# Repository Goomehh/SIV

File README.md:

# SIV

Sistema de identificacion vehicular

# Info

Video presentacion del proyecto: https://youtu.be/XcQt5sAtSic (Principal)

El modelado de la caja y la placa de las conexiones usadas se encuentran en el apartado "Fotos" y "Videos"

# Poster Ingenia Futuro

Poster enfocado a la problematica junto a la propuesta de solucion presentada

# Idea principal del funcionamiento del sistema (flow-chart)

Dos diagramas independientes pero que hacen parte del mismo objetivo.
Como se puede ver en la primera parte del diagrama, el proyecto esta principalemtne orientado a las motos, esto debido a su inidice de hurto en la capital y la accesibilidad que se tiene a sus componentes internos.

Por otro lado esta el sistema de la aplicacion movil, este cuanto mas es parte escencial del proyecto, pues es la que permite el ingreso de nuevos usuarios al sistema y ubica la moto en tiempo real para transmitirlo graficamente

# Boceto superficial del funcionamiento del sistema

Se hace una idea de como puede quedar instalado el circuito en la moto.
De la misma forma se grafica como iria linealmente la secuencia de pasos necesaria para que el motor de la moto sea prendido.

# Diagrama de caja negra

Se plantea lo que viene siendo la alimentacion del circuito y de la misma forma la secuencia adecuada para el procesamiento de los datos, esto teniendo en cuenta el diagrama de flujo que nos explica como debe funcionar el circuito, es necesario tener en cuenta los componenetes principales de cada sector, es decir, los puntos vitales que requiere el circuito, como la alimentacion, el "cerebro", los actuadores, sensores, entre otros.

# Diagrama de caja negra con tecnologia definida

Una vez definida la dinamica y funcionamiento del circuito se empiezan a buscar componentes aptos para facilitar el ensamble, programacion y adaptacion, en nuestro caso usaremos componentes especificos como lo son el Esp32, un sensor de huellas fpm10a, un modulo sim para la tarjeta SD, entre otros (Lista completa en la seccion "Materiales").

# Esquematico del circuito 

En esta seccion se pretende diseñar de forma clara y organizada la conexion de los diferentes componentes que se van a implementar de forma que en caso de requerir fabricar una PCB, no haya mayor complicacion, el circuito fue hecho mediante la aplicacion Kicad.

# Esquematico de la placa PCB

En este esqumatico se puede apreciar la ubicacion de cada uno de los compenetes presentados anteriormente, a excepcion de los pulsadores que simulan al teclado, para este se ponen los puertos para soldar, por otro lado tambien se aprecian las conexiones que se realizan de forma que se ahorra bastante espacio, este tipo de conexiones se manejaron por ambos lados con ese mismo objetivo en mente.

# Vista 3D del a PCB

# Pruebas

A continuacion se anexan algunas fotos sobre los montajes del circuito al vehiculo, sin embargo la mayoria de este archivo multimedia lo puede encontrar en las carpetas designadas.

(Aclaracion: en esta documentacion no esta incluida la PCB mencionada con anterioridad)

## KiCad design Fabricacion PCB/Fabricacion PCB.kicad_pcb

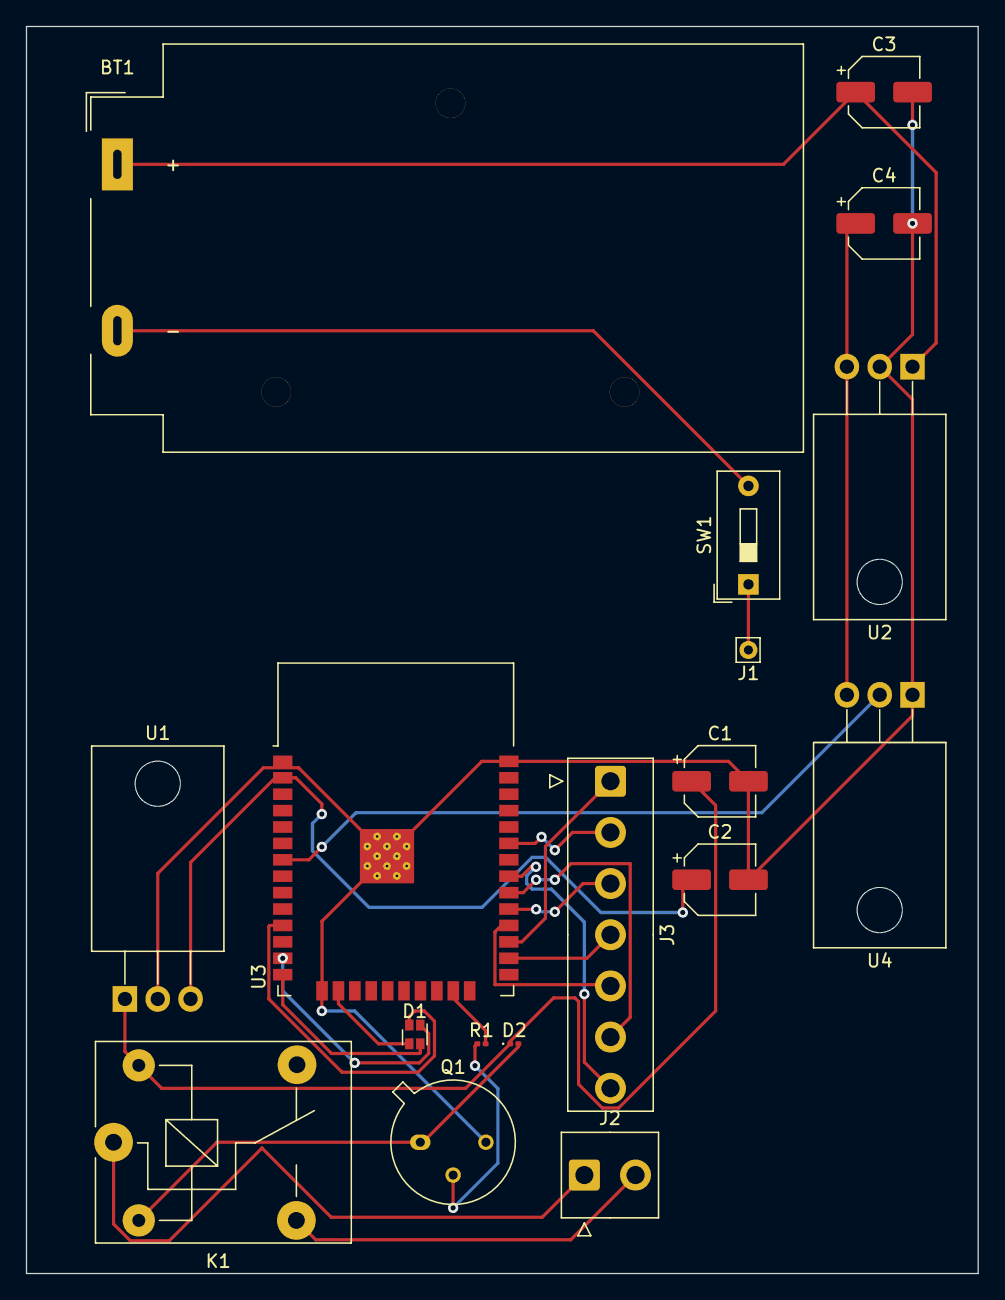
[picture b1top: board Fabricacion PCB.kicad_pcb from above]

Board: 2 copper layers, 73.7 x 96.5 mm, 18 parts (0 on the bottom side), 24 nets.

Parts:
BT1: Battery_Cell; BatteryHolder_MPD_BA9VPC_1xPP3
C1, C2, C3, C4: C_Polarized; CP_Elec_5x5.4
D1: LED_ABGR; LED_LiteOn_LTST-C19HE1WT
D2: D_Zener; LED_0201_0603Metric
J1: Screw_Terminal_01x01; Pin_D0.7mm_L6.5mm_W1.8mm_FlatFork
J2: Screw_Terminal_01x02; TE_826576-2_1x02_P3.96mm_Vertical
J3: Conn_01x07_Socket; TE_826576-7_1x07_P3.96mm_Vertical
K1: SANYOU_SRD_Form_C; Relay_SPDT_SANYOU_SRD_Series_Form_C
Q1: 2N2219; TO-39-3
R1: R_US; R_0201_0603Metric
SW1: SW_SPST; SW_DIP_SPSTx01_Slide_9.78x4.72mm_W7.62mm_P2.54mm
U1, U2: L7805; TO-220-3_Horizontal_TabDown
U3: ESP32-WROOM-32
U4: LM1117T-3.3; TO-220-3_Horizontal_TabDown

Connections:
+12VA: C1.1, D2.1 (K), K1.5, U1.1 (IN)
GND: C1.2, C2.2, C3.2, C4.2, Q1.3 (C), U1.2 (GND), U2.2 (GND), U3.1 (GND), U3.15 (GND), U3.38 (GND), U3.39 (GND), U4.1 (GND)
unnamed: BT1.1 (+), C3.1, U2.1 (IN)
unnamed: BT1.2 (-), SW1.2 (B)
unnamed: D1.1 (A), U3.11 (IO26)
unnamed: D1.2 (BK), U3.13 (IO14)
unnamed: D1.3 (GK), U3.14 (IO12)
unnamed: D1.4 (RK), U3.16 (IO13)
unnamed: D2.2 (A), K1.2, Q1.1 (E)
unnamed: J1.1, SW1.1 (A)
unnamed: J2.1, K1.1
unnamed: J2.2, K1.3
unnamed: J3.1, U3.27 (IO16)
unnamed: J3.2, U3.33 (IO21)
unnamed: J3.3, U3.29 (IO5)
unnamed: J3.4, U3.26 (IO4)
unnamed: J3.5, U3.28 (IO17)
unnamed: J3.6, U3.30 (IO18)
unnamed: J3.7, U3.31 (IO19)
unnamed: Q1.2 (B), R1.1
unnamed: C2.1, U1.3 (OUT), U3.2 (VDD)
unnamed: C4.1, U2.3 (OUT), U4.3 (VI)
unnamed: R1.2, U3.23 (IO15)
unnamed: U3.7 (IO35), U4.2 (VO)

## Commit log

2023-06-23 Create Codigo Esp32
2023-06-24 Videos que pesan menos de 25 mb
2023-06-24 Videos que pesan mas de 25 mb
2023-06-24 Librerias usadas
2023-06-24 Cronologia sensor huellas
2023-06-24 Update Referente al sensor de huellas
2023-06-24 Update and rename Hola.txt to Referente al sensor GPS
2023-06-25 GPS y SIM
2023-06-27 Carcasa
2023-06-27 Rename Referente al sensor GPS y Modulo SIM to Sensor GPS y Modulo SIM
2023-06-27 Rename Referente al sensor de huellas to Sensor de huellas
2023-06-27 Teclado rigido
2023-06-27 Modulo relé y reguladores de voltaje lineal
2023-06-27 Sensor GPS y Modulo SIM
2023-06-27 Sensor de huellas
2023-06-27 Codigo fuente esp32.py to Codigo fuente esp32.py (PRINCIPAL E IMPORTANTE))
2023-06-27 Rename Enroll-ESP.ino to Enroll-ESP.ino (Fallo)
2023-06-27 Gps.ino to Gps.ino (Fallo)
2023-06-27 Sensor huella con microP.py (Fallo)
2023-06-27 Union_sensor_y_gps.ino (Fallo)
2023-06-27 emptyDatabase.ino (Fallo)
2023-06-27 Rename test_with_gps_device.ino to test_with_gps_device.ino (Fallo)
